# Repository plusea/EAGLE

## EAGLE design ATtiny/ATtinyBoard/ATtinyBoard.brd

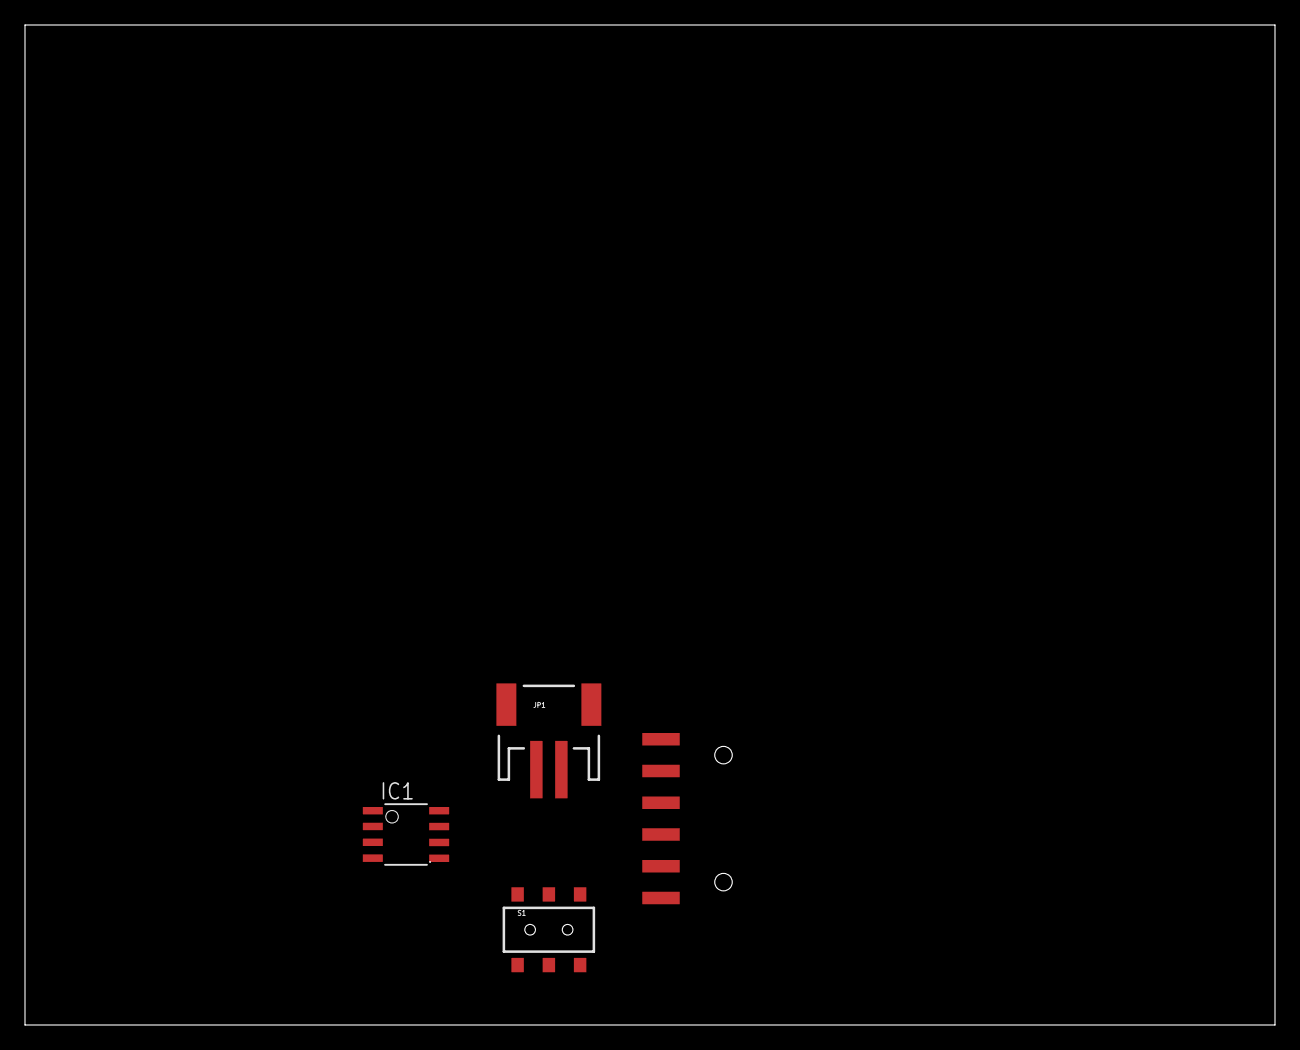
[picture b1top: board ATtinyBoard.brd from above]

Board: 2 copper layers, 100.0 x 80.0 mm, 4 parts (0 on the bottom side), 7 nets, no tracks yet.

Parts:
IC1: TINY13-20SSU; 8S1
ISP/FTDI-CONNECTOR: 1X06-SMD
JP1: M02-JST-2MM-SMT; JST-2-SMD
S1: DPDT; AYZ0202

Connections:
unnamed: IC1.8, ISP/FTDI-CONNECTOR.4
unnamed: IC1.4, ISP/FTDI-CONNECTOR.6
unnamed: IC1.1, ISP/FTDI-CONNECTOR.5
unnamed: IC1.6, ISP/FTDI-CONNECTOR.3
unnamed: ISP/FTDI-CONNECTOR.1, S1.2
unnamed: IC1.5, ISP/FTDI-CONNECTOR.2
unnamed: IC1.7, S1.1

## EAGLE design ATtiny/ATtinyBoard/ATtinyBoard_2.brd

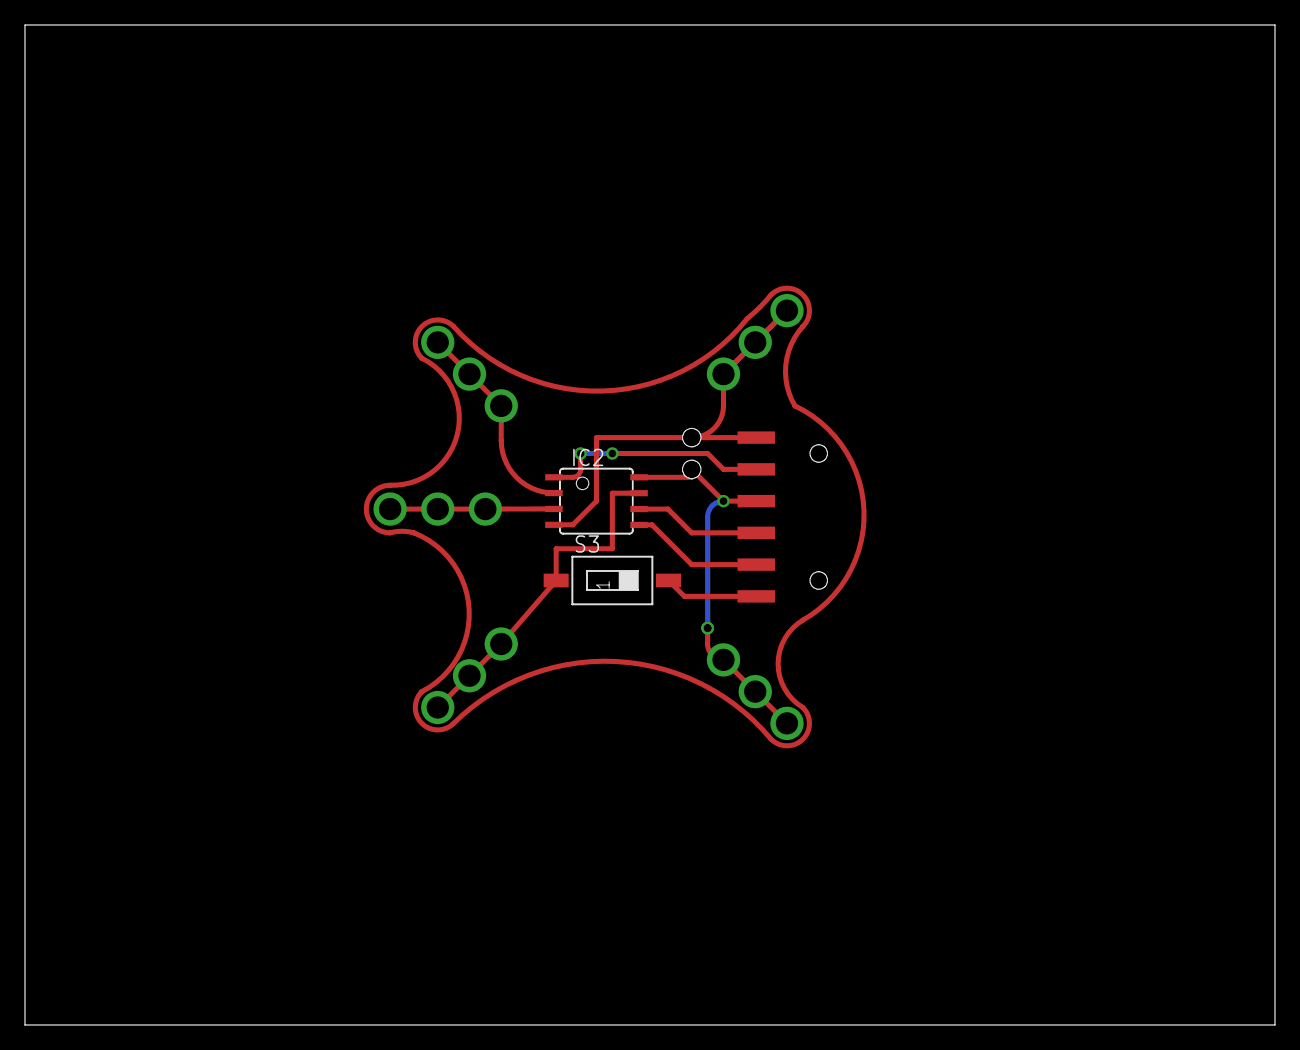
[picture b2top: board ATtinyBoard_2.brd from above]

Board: 2 copper layers, 100.0 x 80.0 mm, 19 parts (0 on the bottom side), 9 nets.

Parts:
H1, H2, H3, H4, H5, H6, H7, H8, H9, H10, H11, H12, H13, H14, H15: SEW_HOLE-SMALL; SIMPLE_HOLE_SM
IC2: TINY13-20SU; 8S2
ISP/FTDI-CONNECTOR: 1X06-SMD
JP2: M02POGO_PIN_HOLES_ONLY; 1X02_PP_HOLES_ONLY
S3: SWS001; SMS-001

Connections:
GND: H4.P$1, H14.P$1, H15.P$1, IC2.4, ISP/FTDI-CONNECTOR.6, JP2.1
unnamed: IC2.5, ISP/FTDI-CONNECTOR.2
unnamed: H3.P$1, H8.P$1, H9.P$1, IC2.3
unnamed: IC2.1, ISP/FTDI-CONNECTOR.5
unnamed: IC2.6, ISP/FTDI-CONNECTOR.3
unnamed: ISP/FTDI-CONNECTOR.1, S3.2
unnamed: H2.P$1, H10.P$1, H11.P$1, IC2.2
unnamed: H5.P$1, H6.P$1, H7.P$1, IC2.8, ISP/FTDI-CONNECTOR.4, JP2.2
unnamed: H1.P$1, H12.P$1, H13.P$1, IC2.7, S3.1

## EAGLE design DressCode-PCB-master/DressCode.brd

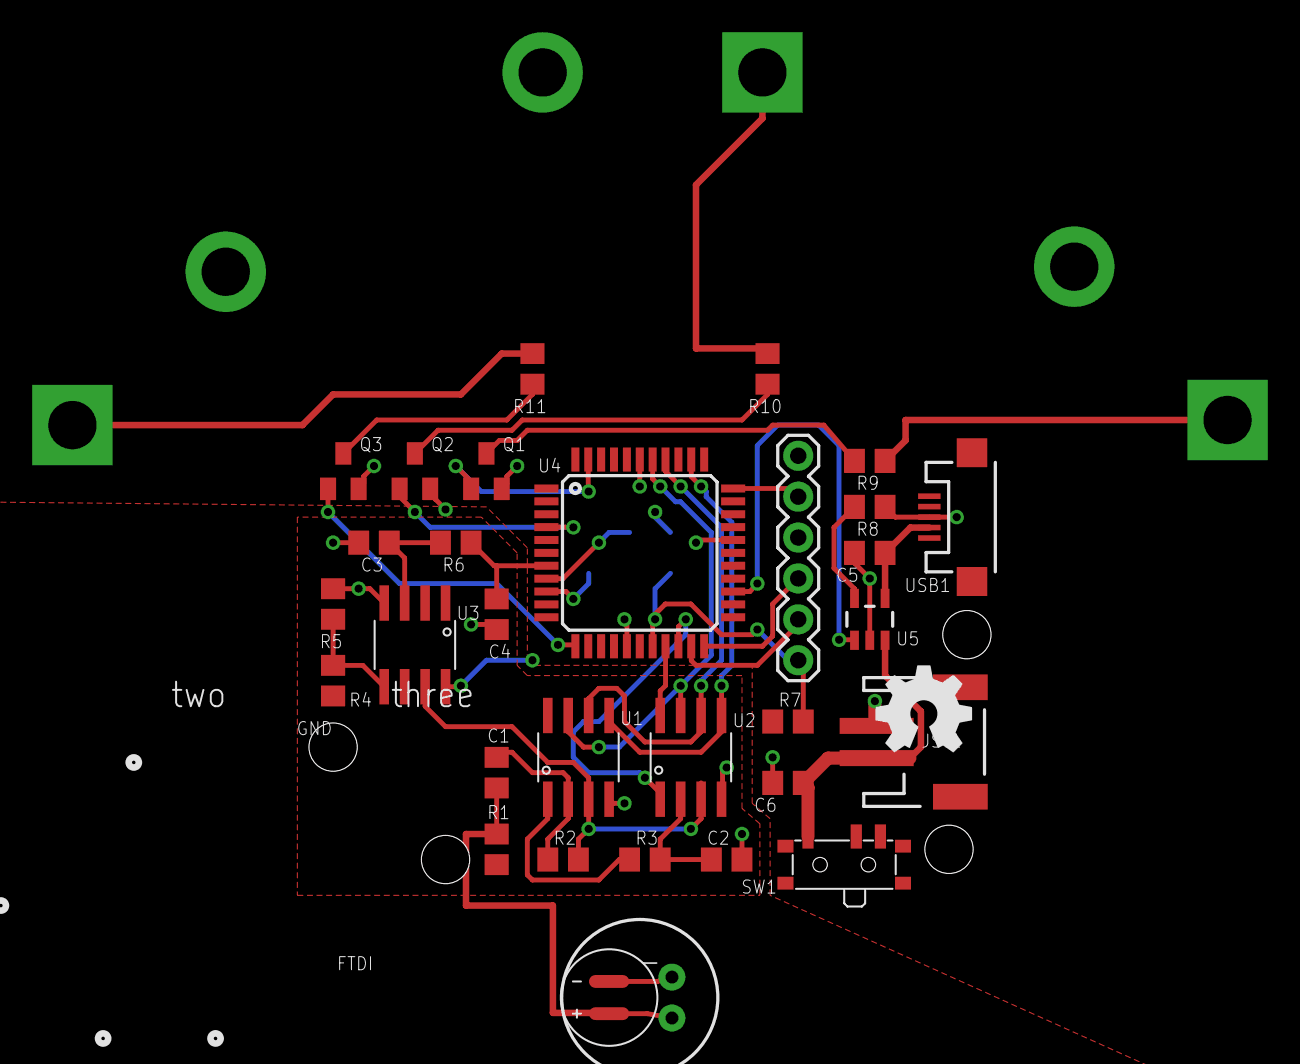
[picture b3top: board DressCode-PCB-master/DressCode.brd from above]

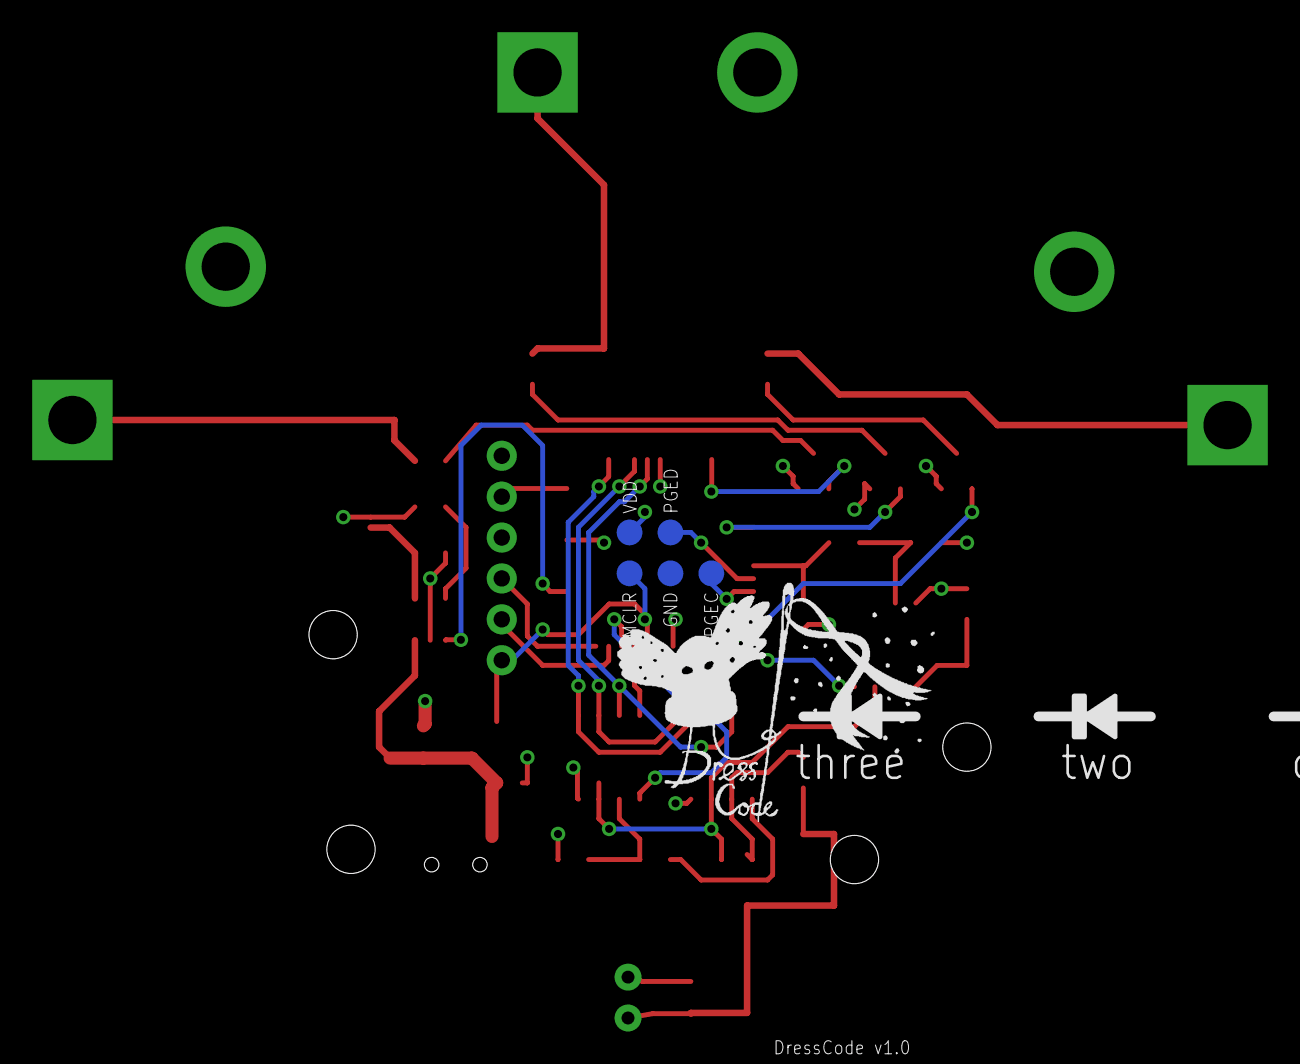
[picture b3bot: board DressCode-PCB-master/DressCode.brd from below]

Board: 2 copper layers, 45 parts (6 on the bottom side), 34 nets.

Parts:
C1, C3, C4, C5, C6: 10u; C0805
C2: 10n; C0805
GND: TPTP16R; TP16R
JP1: 1X06
JST1: JST-2-SMD
M1: MIC9.7MM; MIC-9.7MM
M2: MIC6MM; MIC-SMD
MCLR: TPTP16R; TP16R
PGEC: TPTP16R; TP16R
PGED: TPTP16R; TP16R
Q1, Q2, Q3: 2N7002; SOT23
R1, R2, R3, R4, R5, R6, R7, R8: 2.2k; R0805
R9, R10, R11: 100R; R0805
SW1: PCM12SMTR
U1, U2: MCP6S21; SOIC-8
U3: MCP6G02; SOIC-8
U4: PIC24FV32KA304-I/PT; TQFP44
U5: MCP73832T-2ACI/OT; SOT23-5
U$1: OSHW_LOGO_6MM_BOTTOM
U$2: DRESSCODE-OUTLINE1
U$4, U$5, U$6: DRESSCODE_SEW_PADC; DRESSCODE_SEW_PAD_CIRC
U$7, U$8, U$10: DRESSCODE_SEW_PADS; DRESSCODE_SEW_PAD_SQR
U$9: DRESSCODE_LOGO
USB1: USB-MICROB
VDD: TPTP16R; TP16R

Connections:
ADC: U2.1, U4.20
AVDD: R1.2, R4.2, U1.8, U2.8, U3.1, U4.19
AVDD_REF: C4.2, R6.1, U4.7
BATT: C6.2, JST1.2, SW1.1, U5.3
CS: U1.5, U2.5, U4.35
FTDI_RX: JP1.5, U4.21
FTDI_TX: JP1.4, U4.22
GND: C2.2, C3.1, C4.1, C5.1, C6.1, GND.TP, JP1.1, JST1.1, M1.2, M2.-, Q1.2, Q2.2, Q3.2, R5.1, R8.1, U1.4, U2.4, U3.4, U4.16, U4.29, U4.39, U5.2, USB1.D+
MCLR: JP1.6, MCLR.TP, R7.1, U4.18
unnamed: C1.1, M1.1, M2.+, R1.1
unnamed: C1.2, R2.1, U1.2
unnamed: C2.1, R3.2, U2.2
unnamed: R3.1, U1.1
unnamed: C3.2, R6.2, U3.3
unnamed: R4.1, R5.2, U3.5
unnamed: Q1.3, R9.1
unnamed: Q2.3, R10.1
unnamed: Q3.3, R11.1
unnamed: R9.2, U$7.1
unnamed: R10.2, U$8.1
unnamed: R11.2, U$10.1
unnamed: R8.2, U5.5
PGEC: PGEC.TP, U4.9
PGED: PGED.TP, U4.8
PWM1: Q1.1, U4.43
PWM2: Q2.1, U4.4
PWM3: Q3.1, U4.12
RB4: JP1.2, U4.33
SI: U1.6, U2.6, U4.37
SLK: U1.7, U2.7, U4.38
STAT: U4.25, U5.1
USB1: C5.2, U5.4, USB1.D-
VDD: JP1.3, R7.2, SW1.2, U3.8, U4.17, U4.28, U4.40, U$4.1, U$5.1, U$6.1, VDD.TP
VREF: R2.2, U1.3, U2.3, U3.7

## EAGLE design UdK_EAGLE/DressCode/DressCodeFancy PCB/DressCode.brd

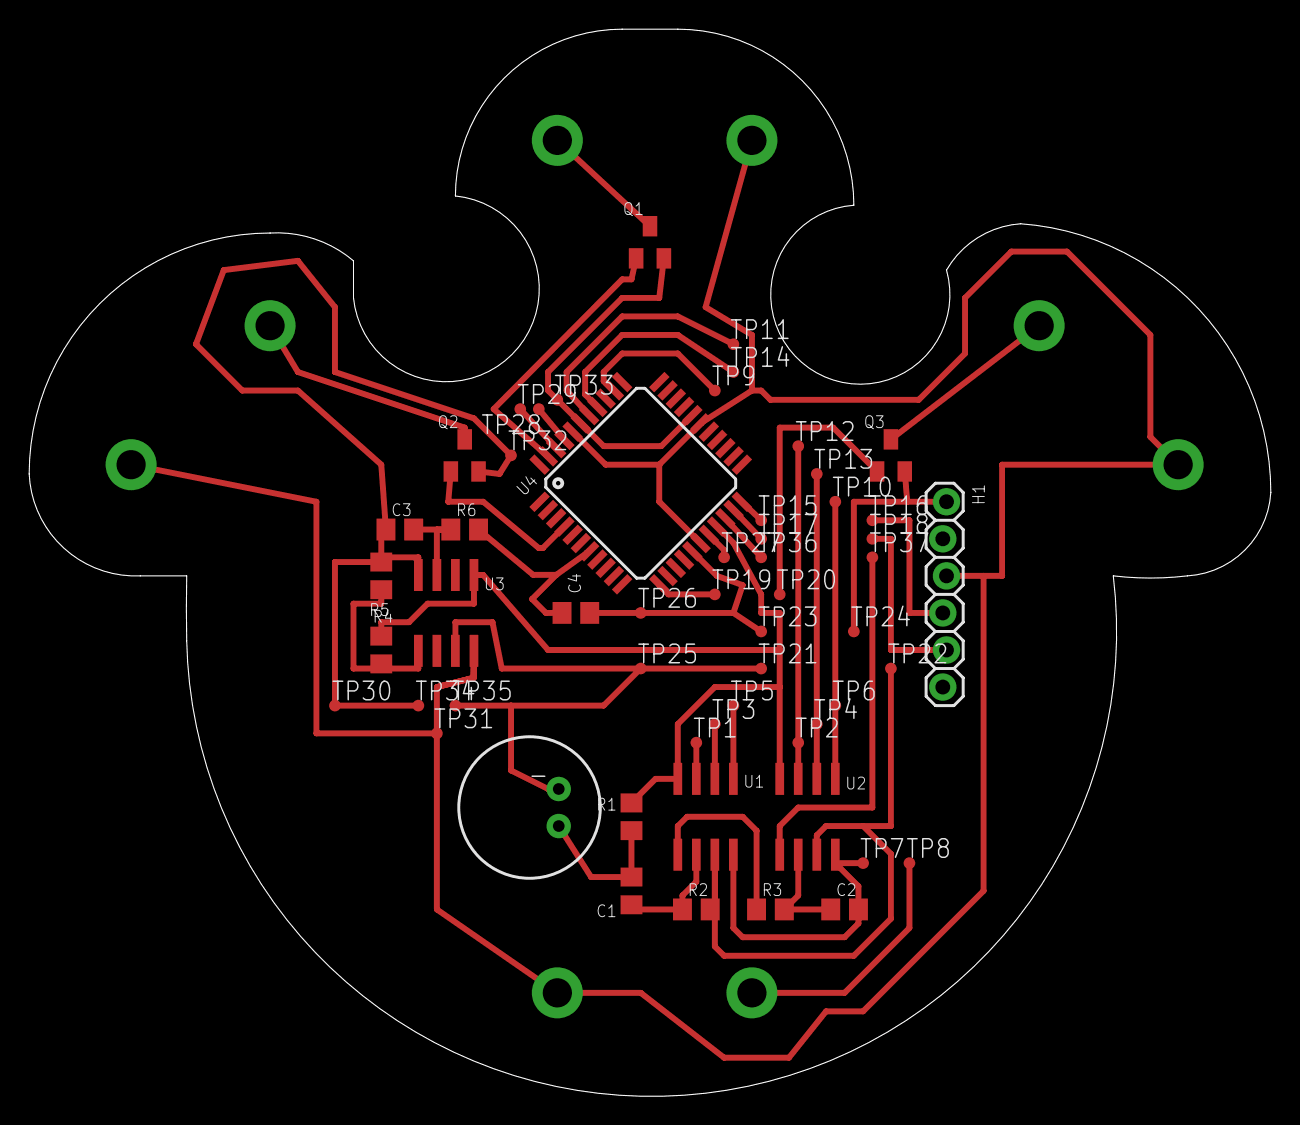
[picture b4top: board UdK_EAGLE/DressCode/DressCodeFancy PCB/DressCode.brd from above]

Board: 2 copper layers, 85.1 x 73.1 mm, 57 parts (0 on the bottom side), 23 nets.

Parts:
C1, C3, C4: 10u; C0805
C2: 10n; C0805
H1: 1X06_LOCK
M1: MIC9.7MM; MIC-9.7MM
Q1, Q2, Q3: 2N7002; SOT23
R1, R2, R3, R4, R5, R6: 2.2k; R0805
TP1, TP2, TP3, TP4, TP5, TP6, TP7, TP8, TP9, TP10, TP11, TP12, TP13, TP14, TP15, TP16, TP17, TP18, TP19, TP20, TP21, TP22, TP23, TP24, TP25, TP26, TP27, TP28, TP29, TP30, TP31, TP32, TP33, TP34, TP35, TP36, TP37: TPTP08R; TP08R
U1, U2: MCP6S21; SOIC-8
U3: MCP6G02; SOIC-8
U4: PIC24FV32KA304-I/PT; TQFP44
U$1: DRESSCODE-OUTLINE1

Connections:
ADC: TP36.TP, TP37.TP, U2.1, U4.20
AVDD: R1.2, R4.2, U1.8, U2.8, U3.1, U4.19
AVDD_REF: C4.2, R6.1, U4.7
CS: TP5.TP, TP6.TP, TP9.TP, TP10.TP, U1.5, U2.5, U4.35
FTDI_RX: H1.5, TP17.TP, TP18.TP, U4.21
FTDI_TX: H1.4, TP15.TP, TP16.TP, U4.22
GND: C2.2, C3.1, C4.1, H1.1, M1.2, Q1.2, Q2.2, Q3.2, R5.1, TP7.TP, TP8.TP, TP23.TP, TP24.TP, TP25.TP, TP26.TP, TP30.TP, TP32.TP, TP33.TP, TP34.TP, TP35.TP, U1.4, U2.4, U3.4, U4.16, U4.29, U4.39
MCLR: TP27.TP, U4.18
unnamed: C1.1, M1.1, R1.1
unnamed: C1.2, R2.1, U1.2
unnamed: C2.1, R3.2, U2.2
unnamed: R3.1, U1.1
unnamed: C3.2, R6.2, U3.3
unnamed: R4.1, R5.2, U3.5
PGEC: TP29.TP, U4.42
PGED: TP28.TP, U4.41
PWM1: Q1.1, U4.43
PWM2: Q2.1, U4.4
PWM3: Q3.1, TP19.TP, TP20.TP, U4.12
SI: TP3.TP, TP4.TP, TP13.TP, TP14.TP, U1.6, U2.6, U4.37
SLK: TP1.TP, TP2.TP, TP11.TP, TP12.TP, U1.7, U2.7, U4.38
VDD: H1.3, TP31.TP, U3.8, U4.17, U4.28, U4.40
VREF: R2.2, TP21.TP, TP22.TP, U1.3, U2.3, U3.7

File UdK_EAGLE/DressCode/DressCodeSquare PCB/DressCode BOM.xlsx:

| Name | Device | Qty | Unit price | Total price
 | R1, R2, R3, R4, R5, R6 | 2.2k, 0805 | 6 | 1.4999999999999999E-2 | 0.09
 | C1, C3, C4 | 10u, 0805 | 3 | 0.02 | 0.06
 | Q1, Q2, Q3 | 2N7002 (N-channel FET) | 3 | 2.7E-2 | 8.1000000000000003E-2
 | U3 | MCP6G02 (SGA) | 1 | 0.314 | 0.314
 | U1, U2 | MCP6S21 (PGA) | 2 | 0.68600000000000005 | 1.3720000000000001
 | M1 | Microphone | 1 | 0.46400000000000002 | 0.46400000000000002
 | U4 | PIC24FV32KA304-I/PT | 1 | 1.91 | 1.91
 |  |  |  | Total: | 4.2910000000000004

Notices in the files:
parts and their libraries:
SparkFun-Electromechanical: Licensing: CC v3.0 Share-Alike You are welcome to use this library for commercial purposes.
